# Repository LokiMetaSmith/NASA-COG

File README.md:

# NASA-MCOG

## Final Report

The final report delivered to NASA for this project can be [read here](https://drive.google.com/file/d/1jfJcSLfsybuC49I7llPhfTNI8ucRUW3h/view?usp=sharing).

## Introduction

This is a repo for a control system made for NASA to drive a Ceramic Oxygen Generation
technology they have developed. It was forked from ["The Ox"]() project of Public Invention run by Mr. Ben Coombs, which was in turn a fork of the VentOS project of Helpful Engineering led by Ben Coombs, Dr. Erich Schulz, and Robert L. Read.

However, the main reason we are starting with this fork is not that the Pressure Swing
Adsorption system of the Ox is a particularly relevant, but rather that the code
represents a nice platform of simple (microcontroller) control of related machines.

To wit, includes PlatformIO configuration, a state machine (finite automata),
a superloop architecture, and a hardware abstraction layer.

This particular project of NASA will improve life support technology in space,
but may eventually greatly improve global health.

An unlisted [YouTube video](https://youtu.be/1nq-Mw7jZ5A) has been uploaded that shows this work in-progress as of September 2022.

## How to run

### Linux
The fundamental way to run this is to perform:  
> cd firmware  
> pio run -e native && ./.pio/build/native/program  
We are currently creating the [RibbonFish](https://github.com/PubInv/NASA-COG/blob/develop/RibbonFish.md) proof-of-concept.
This can be run on a Due by executing:  
> make pio-run-due_ribbonfish  
As this develops, it will use a specific Due hardware configuration,  
please see the [documentation](https://github.com/PubInv/NASA-COG/blob/develop/RibbonFish.md) for details to build your own.  

### Windows
With Powershell
Navigate to the firmware folder. 
Type: pio run -e due_ribbonfish

With Visual Studio Code.  
Install the Plateform IO extension  
To open the project in Visual Studio Code.  
Open Project. Navigate to the firmware folder.   
Select the file platformio.ini  
Press the build check mark on the bottom of the window.

To disable the automatic load and serial monitor comment out the lines with "targets = upload, monitor" in the file "platformio.ini"

## Annoyances

AFAIK, PlatformIO forces a directory tree depth of 5 levels.

This is not enough to organize the Hardware Abstraction Level the way I would prefer, forcing us to make some messy directories that are less than clear.

For example, to implement a Temperature Sensor, we would ideally have an
abstract (or virtual) implementation, a folder for real hardware,
and a folder for mock sensors.  I have no choice now but to jam
the mock sensors into the same directory with the real hardware and
use a naming convention to differentiate them.

## The Command System

The NASA-COG system needs to allow the user to enter commands. The most obvious of these is "turn off".
Because the system should avoid thermal shocks, this is actually not simple.

We have previously used an [approach](https://github.com/PubInv/PIRCS-pubinv-respiration-control-standard) of using simple JSON objects to represent commands. We propose to use the same idea here, but obviously,
the command will be custom to the NASA-COG.

### Parameter Setting Commands
The general scheme is to use a JSON object like:

```JavaScript
{ "com": "T",
  "par": 7,
  "mod": "T",
  "val" : 732.3
  }
```

1. "com" is the command. For example, "T" can mean "set Temperature".
2. "par" is a parameter used to specify something about how to execute the command. For example, 7 could mean location 7, which might be between the 6th and 7th stack.
3. "mod" is a modifier of the command. For example, the "set Temperature" command could be used to
set the minimum, maximum, or the target temperature.
4. "val" is the value that is to be set.

For this problem space, we can specify some global parameters of the problem, some of which
involve safety. These can of course have default values "hard wired" into the code, but an
experimenter may wish to change these values (carefully).

1. The maximum rate of voltage change applied to a stack. Nominally we have defined this as 1 volt/second.
We have evidence that too rapid a voltage change (such as that caused by pulse-width modulation) can destroy
a stack.
2. The maximum rate of temperature change for a stack. Nominally we may say this as 2 degree K per minute,
which would allow the machine to reach operating temperature in 6 hours.
3. The maximum temperature difference across a stack in any dimension. We may not be able to control
this directly, but we can use it as a target.
4. The maximum voltage applied to a stack.
5. The maximum amperage applied to a stack.

### Event-like Commands

We will need other commands that represent discrete events in time. For example, each transition in the
state transition diagram below may be initiated by a command from the user (they may also occur
automatically due to an internal fault or even normal operation.)

We can implement particular commands with the same scheme.

For example, the simple object:

```JavaScript
{ "com": "C",
  "par": 0,
  "int": "s",
  "mod": "U",
  "val" : 0.0
  }
```

Could mean "Cool Down". The value "U" is used becasue the "mod" command is "unusued" in this case.

```JavaScript
{ "com": "W",
  "par": M,
  "int": "s",
  "mod": "U",
  "val" : 0.0
  }
```

In actual practice, these commands will be pasted into the serial port using either PlatformIO or the Arduino IDE.

Eventually, a user interface may be implemented that uses a knob or a nice webpage to enter commands.
However, by having each of these take only actions that can be implemented as such a command,
we bring discipline to the internal code.

## Actual Serial Commands

The serial port currently supports 6 one-character commands: w,c,e,a,i,o.
These mean:
1. warmup
2. cool down
3. emergency shutdown
4. acknowledge
5. idle
6. operate

Note: "acknowledge" means that the operator acknowledges that a critical
state has occurred and asserts it is okay to return to normal operation,
either because the problem as been removed or for some other reason.

Addtionally, the system supports "full commands", that look like this:

> { "com": "W", "par": "M", "int": "s", "mod": "U", "val" : 0.0 }

> { "com": "C", "par": "M", "int": "s", "mod": "U", "val" : 0.0 }

> { "com": "E", "par": "M", "int": "s", "mod": "U", "val" : 0.0 }

> { "com": "A", "par": "M", "int": "s", "mod": "U", "val" : 0.0 }

> { "com": "I", "par": "M", "int": "s", "mod": "U", "val" : 0.0 }

> { "com": "O", "par": "M", "int": "s", "mod": "U", "val" : 0.0 }

In fact, each "one character" command is a short hand for these commands.

The following format can be used to set parameters (P).
The three most important parameters are:
1. T : Temperature (in C) going into the stack
2. C : Current (in milliamps) going into the stack
3. F : Fan speed in RPM (we expect this to change to flow rate in SLM)
> { "com": "P", "par": "T", "int": "T", "mod": "U", "val" : 35 }

> { "com": "P", "par": "C", "int": "T", "mod": "U", "val" : 500 }

> { "com": "P", "par": "F", "int": "T", "mod": "U", "val" : 2000 }

These three commands set the:
1. Temperature into the stack to 35C
2. Set the Target current into the stack to 500 milliamps
3. Set the flow rate to 2000 ml/seconds

## License

In general we intend to follow the [Public Invention Licensed Guidelines](https://github.com/PubInv/PubInv-License-Guidelines) unless
NASA requests something different. If you are starting your own project, please
feel free to fork the license guidelines as a starting point if you like our
license policy.

This program includes free software: you can redistribute it and/or modify it under the terms of the GNU Affero General Public License as published by the Free Software Foundation, either version 3 of the License, or (at your option) any later version.

See the GNU Affero General Public License for more details. You should have received a copy of the GNU Affero General Public License along with this program. If not, see <https://www.gnu.org/licenses/>.

This program is distributed in the hope that it will be useful, but WITHOUT ANY WARRANTY; without even the implied warranty of MERCHANTABILITY or FITNESS FOR A PARTICULAR PURPOSE.

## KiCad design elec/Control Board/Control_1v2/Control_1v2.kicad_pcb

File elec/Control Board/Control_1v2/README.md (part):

# Contents of This Folder Copyed. MAKE NO MORE CHANGES HERE
See: https://github.com/PubInv/high-amp-controller-board
Copied on date: 20250526

<hr>
# Control V1.1 aka 1V1
Version 1.1 control board for NASA COG

On line schematic viewing from **Kicanvas** See: https://kicanvas.org  
The Control V1 is an Arduino DUE "Shield". The DUE will live below this printed wiring assembly. An Ethernet shield will live above as a "Socket". See KiCad Symbol & Footprint Library for Arduino Modules for "Shield" and "Socket"

## Schematics
### Browser page view of the schematic by KiCanvas.org 
Top page is "Control v1.kicad_sch". Note the page for MAX31856 is actualy for an MCP9600 but the page was not renamed (as of 20230830)
*  [Control1v1.kicad_sch](https://kicanvas.org/?github=https%3A%2F%2Fgithub.com%2FPubInv%2FNASA-COG%2Fblob%2Fdevelop%2Felec%2FControl%2520Board%2FControl_1v1%2FControl_1v1%2FControl_1v1.kicad_sch)
* [Adafruit-MAX31850-thermocouple-breakout-board.kicad_sch](https://kicanvas.org/?github=https%3A%2F%2Fgithub.com%2FPubInv%2FNASA-COG%2Fblob%2Fdevelop%2Felec%2FControl%2520Board%2FControl_1v1%2FControl_1v1%2FAdafruit-MAX31850-thermocouple-breakout-board.kicad_sch)
* [Adafruit-MAX31855-breakout-board.kicad_sch](https://kicanvas.org/?github=https%3A%2F%2Fgithub.com%2FPubInv%2FNASA-COG%2Fblob%2Fdevelop%2Felec%2FControl%2520Board%2FControl_1v1%2FControl_1v1%2FAdafruit-MAX31855-breakout-board.kicad_sch)
* [Adafruit-MAX31856-PCB-master.kicad_sch](https://kicanvas.org/?github=https%3A%2F%2Fgithub.com%2FPubInv%2FNASA-COG%2Fblob%2Fdevelop%2Felec%2FControl%2520Board%2FControl_1v1%2FControl_1v1%2FAdafruit-MAX31856-PCB-master.kicad_sch)
* [Fan controller.kicad_sch](https://kicanvas.org/?github=https%3A%2F%2Fgithub.com%2FPubInv%2FNASA-COG%2Fblob%2Fdevelop%2Felec%2FControl%2520Board%2FControl_1v1%2FControl_1v1%2FFan%2520controller.kicad_sch)
* [I2C_Level_Shifter.kicad_sch](https://kicanvas.org/?github=https%3A%2F%2Fgithub.com%2FPubInv%2FNASA-COG%2Fblob%2Fdevelop%2Felec%2FControl%2520Board%2FControl_1v1%2FControl_1v1%2FI2C_Level_Shifter.kicad_sch)
* [SPI_ControllerLevel_Shifter.kicad_sch](https://kicanvas.org/?github=https%3A%2F%2Fgithub.com%2FPubInv%2FNASA-COG%2Fblob%2Fdevelop%2Felec%2FControl%2520Board%2FControl_1v1%2FControl_1v1%2FSPI_ControllerLevel_Shifter.kicad_sch)
* [SSR Interface.kicad_sch](https://kicanvas.org/?https%3A%2F%2Fgithub.com%2FPubInv%2FNASA-COG%2Fblob%2Fdevelop%2Felec%2FControl+Board%2FControl+v1%2FSSR+Interface.kicad_sch=&github=https%3A%2F%2Fgithub.com%2FPubInv%2FNASA-COG%2Fblob%2Fdevelop%2Felec%2FControl%2520Board%2FControl%2520v1%2FSSR%2520Interface.kicad_sch)
* [display_interface.kicad_sch](https://kicanvas.org/?github=https%3A%2F%2Fgithub.com%2FPubInv%2FNASA-COG%2Fblob%2Fdevelop%2Felec%2FControl%2520Board%2FControl_1v1%2FControl_1v1%2Fdisplay_interface.kicad_sch)

## PCB / PWA
### Browser page view of the PCB by KiCanvas.org 
Printed Circuit Board, Printed Wiring Assembly
* [Control 1v1.kicad_pcb](https://kicanvas.org/?github=https%3A%2F%2Fgithub.com%2FPubInv%2FNASA-COG%2Fblob%2Fdevelop%2Felec%2FControl%2520Board%2FControl_1v1%2FControl_1v1%2FControl_1v1.kicad_pcb)

### PCB / PWA 3D Snapshot

### BOM and Parts List
File Notes:
See notes on the Gerbers, BOM and placement files at:
https://github.com/PubInv/NASA-COG/issues/342

## License, Public Invention for this PCB, PWA
* [Firmware: Affero GPL 3.0](https://www.gnu.org/licenses/agpl-3.0.en.html#license-text)
* [CERN Open Hardware Licence Version 2 - Strongly Reciprocal](https://ohwr.org/cern_ohl_s_v2.txt)

<hr> 

## KiCad Symbol & Footprint Library for Arduino Modules
<a href="./PICS/Rev2/PWA_FrontView.png">  
*Version 4.1.0*  

This is a library of KiCad schematic symbols and PCB footprints for most Arduino modules. You can use them to make your own PCB design which will effortlessly connect with your chosen Arduino module.

Currently included modules:
- Arduino **101** Shield
- Arduino **Due** Shield
- Arduino **Giga R1 WiFi** Shield
- Arduino **Leonardo** Shield
- Arduino **M0** Shield
- Arduino **M0 Pro** Shield
- Arduino **Mega 2560 R3** Shield
- Arduino **Micro** Socket
- Arduino **Mini** Socket
- Arduino **MKR 1000 WiFi** Socket
- Arduino **MKR WiFi 1010** Socket
- Arduino **MKR FOX 1200** Socket
- Arduino **MKR WAN 1300** Socket
- Arduino **MKR WAN 1310** Socket
- Arduino **MKR GSM 1400** Socket
- Arduino **MKR NB 1500** Socket
- Arduino **MKR Vidor 4000** Socket
- Arduino **MKR Zero** Socket
- Arduino **Nano** Socket
- Arduino **Nano 33 BLE** Socket / Tile
- Arduino **Nano 33 BLE Sense** Socket / Tile
- Arduino **Nano 33 BLE Sense R2** Socket / Tile
- Arduino **Nano 33 IoT** Socket / Tile
- Arduino **Nano Every** Socket / Tile
- Arduino **Nano RP2040 Connect** Socket / Tile
- Arduino **Nicla Sense ME** Socket / Tile
- Arduino **Nicla Vision** Socket / Tile
- Arduino **Nicla Voice** Socket / Tile
- Arduino **Pro Mini** Socket
- Arduino **Uno R1** Shield
- Arduino **Uno R2** Shield
- Arduino **Uno R3** Shield
- Arduino **Uno R3 SMD** Shield
- Arduino **Uno R4 Minima** Shield
- Arduino **Uno R4 WiFi** Shield
- Arduino **Uno WiFi R2** Shield
- Arduino **Zero** Shield
- Clone **Mega 2560 Pro** Socket
- Clone **Pro Mini** Socket

*"Shield" means the module is designed to plug in from beneath your PCB. "Socket" means the module is designed to plug in from above your PCB. "Tile" means the module is designed to be soldered directly on to your PCB using surface-mount pads.*

## KiCad Version Compatibility
This library requires at least KiCad 6 to function, and is tested on KiCad versions 6.0.8 and 7.0.2. Note that the installation procedure is different for KiCad 6 and 7; please see the [Library Installation](#library-installation) section below.

## Comments, Requests, Bugs & Contributions
All are welcome!
Please open an [Issue](https://github.com/Alarm-Siren/arduino-kicad-library/issues) or [Pull Request](https://github.com/Alarm-Siren/arduino-kicad-library/pulls), as appropriate.

## Library Installation
To install this library in your copy of KiCad, choose the correct section for your version of KiCad and follow the steps given. These instructions only cover automated installation using KiCad's built-in Package and Content Manager (PCM); manual installation is possible but not supported.

### KiCad 7

**Warning**: Do not change the nickname prefix from that given in step 4 below. If you do so KiCad will not assign the correct footprints to the symbols by default.

1. Open KiCad and open the Preferences window at "Preferences" -> "Preferences..."
2. Select the "Plugin and Content Manager" section in the left-hand pane.
3. Ensure that the "Automatically add installed libraries to the global lib table" option is ticked.
4. Ensure that the "Library nickname prefix" is set to "PCM_".
5. Ensuring that the "Check for package updates on startup" option is ticked is recommended. **(Optional)**
6. Click "OK" to close the Preferences window.
7. Click the "Plugin and Content Manager" button.
8. Select the "KiCad official repository" from the top drop-down box (if not already selected).
9. Go the Libraries tab and locate the "KiCad Library for Arduino Modules" in the list.
10. Click the "Install" button for that entry in the list.
11. Click "Apply Pending Changes".
12. Close the "Applying Package Changes" window once it has finished.
13. You should now find that this library is listed in the "Installed" tab.
14. Close the Plugin and Content Manager.
15. You may need to restart KiCad for the library installation to fully take effect. **(Optional)**
16. All done: you are now ready to use these schematic components and footprints in your projects!

### KiCad 6
**Recommendation:** If you can, you should upgrade to KiCad 7.

**Warning**: Do not change the Nicknames from those given in steps 12 and 18 below. If you do so KiCad will not assign the correct footprints to the symbols by default.

1. Open KiCad and click the "Plugin and Content Manager" button.
2. Select the "KiCad official repository" from the top drop-down box (if not already selected).
3. Go the Libraries tab and locate the "KiCad Library for Arduino Modules" in the list.
4. Click the "Install" button for that entry in the list.
5. Click "Apply Changes".
6. Close the "Applying Package Changes" window once it has finished.
7. You should now find that this library is listed in the "Installed" tab.
8. Close the Plugin and Content Manager.
9. Go to the "Preferences" -> "Manage Symbol Libraries..." menu option.
10. In the Symbol Libraries dialogue that appears, switch to the "Global Libraries" tab (if not already selected).
11. Click "Add empty row to table" button (the button with a big cross in it, beneath the table).
12. In the new line of the table, set the Nickname to "PCM_arduino-library", and ensure the Library Format is set to "KiCad".
13. In the same line of the table, set Library Path to "${KICAD6_3RD_PARTY}/symbols/com_github_alarm-siren_arduino-kicad-library/arduino-library.kicad_sym".
14. Click "OK" to close the Symbol Libraries dialogue.
15. Go to "Preferences" -> "Manage Footprint Libraries..." menu option.
16. In the Footprint Libraries dialogue that appears, switch to the "Global Libraries" tab (if not already selected).
17. Click "Add empty row to table" button (the button with a big cross in it, beneath the table).
18. In the new line of the table, set the Nickname to "PCM_arduino-library", and ensure the Library Format is set to "KiCad".
19. In the same line of the table, set Library Path to "${KICAD6_3RD_PARTY}/footprints/com_github_alarm-siren_arduino-kicad-library/arduino-library.pretty".
20. Click "OK" to close the Footprint Libraries dialogue.
21. All done: you are now ready to use these schematic components and footprints in your projects!

## Donations

I really hope you've found this library useful. If you'd like to buy me a beer in thanks for the work I put into it, you can make a donation using the button below:

## License & Legal
Copyright 2017-2023, [Nicholas Parks Young](https://github.com/Alarm-Siren).

Except as otherwise noted, all content of this library is licensed under the 
[Creative Commons Attribution-ShareAlike 4.0 International License](https://creativecommons.org/licenses/by-sa/4.0/), with the following additional exception:
> To the extent that the creation of electronic designs that use the Licensed Material can be considered to be Adapted Material, the Licensor waives Section 3 of the Public License with respect to these electronic designs and any generated files which incorporate data provided as part of the Licensed Material.

### "KiCad Library for Arduino" Banner & Icon

The two images "resources/banner.png" and "resources/icon.png" are licensed under the [Creative Commons Attribution-NonCommercial-ShareAlike 4.0 International License](https://creativecommons.org/licenses/by-nc-sa/4.0/). These images are derivatives of ["Arduino Open-Source Community: Main Logotype RGB Colors" originally created by Arduino](https://www.arduino.cc/en/trademark/community-logo). 

Original Images: Copyright 2013, [Arduino](https://www.arduino.cc/). Derived Images: Copyright 2023, [Nicholas Parks Young](https://github.com/Alarm-Siren).

### Arduino Trademark

The word "Arduino" is a registered trademark of [Arduino](https://www.arduino.cc/). This trademark is used in this library to refer to Arduino products and to identify Arduino-related non-commercial content, as permitted by Arduino's [trademark guidelines](https://www.arduino.cc/en/trademark). This project is not affiliated with nor endorsed by Arduino.

## FAQ

Answers to some common questions about this library.

### Is this library in active development?

Yes. For the foreseeable future, I will be providing support, bug-fixes and updating the library with any new Arduino modules as they are released.

### What does the license exception in the License & Legal section mean?

This library uses the same license as KiCad's own built-in parts library does, including the exception. The KiCad Libraries team have a [page which explains the meaning of the exception](https://www.kicad.org/libraries/license/). My version of the exception uses slightly better wording, but the effect is the same.

### Why do the footprints not have an `Edge.Cuts` outline?

If I put in an `Edge.Cuts` outline, then those users who want to have a PCB larger than the module footprint would have to modify the footprint to do so. In my experience, it is far more common for users to want a PCB larger than the module anyway, so I prefer to cater to those users. If you want your PCB to be the same size and shape as the Arduino module, you can trace the `F.Silkscreen` or `B.Silkscreen` layer (as appropriate) out in the `Edge.Cuts` layer yourself, or you can modify the footprint to change the outline from `F.Silkscreen` or `B.Silkscreen` layer to `Edge.Cuts`.

### Why do the Nicla Vision and Nicla Voice tile footprints have cut-outs?

The cut-outs are necessary to accommodate components on the back of those modules; without them the components would physically prevent you from getting the module's pads down to the footprint's SMD pads.

### Why does the whole footprint have an `F.Courtyard` or `B.Courtyard` outline? I can't place my components where I need to!

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
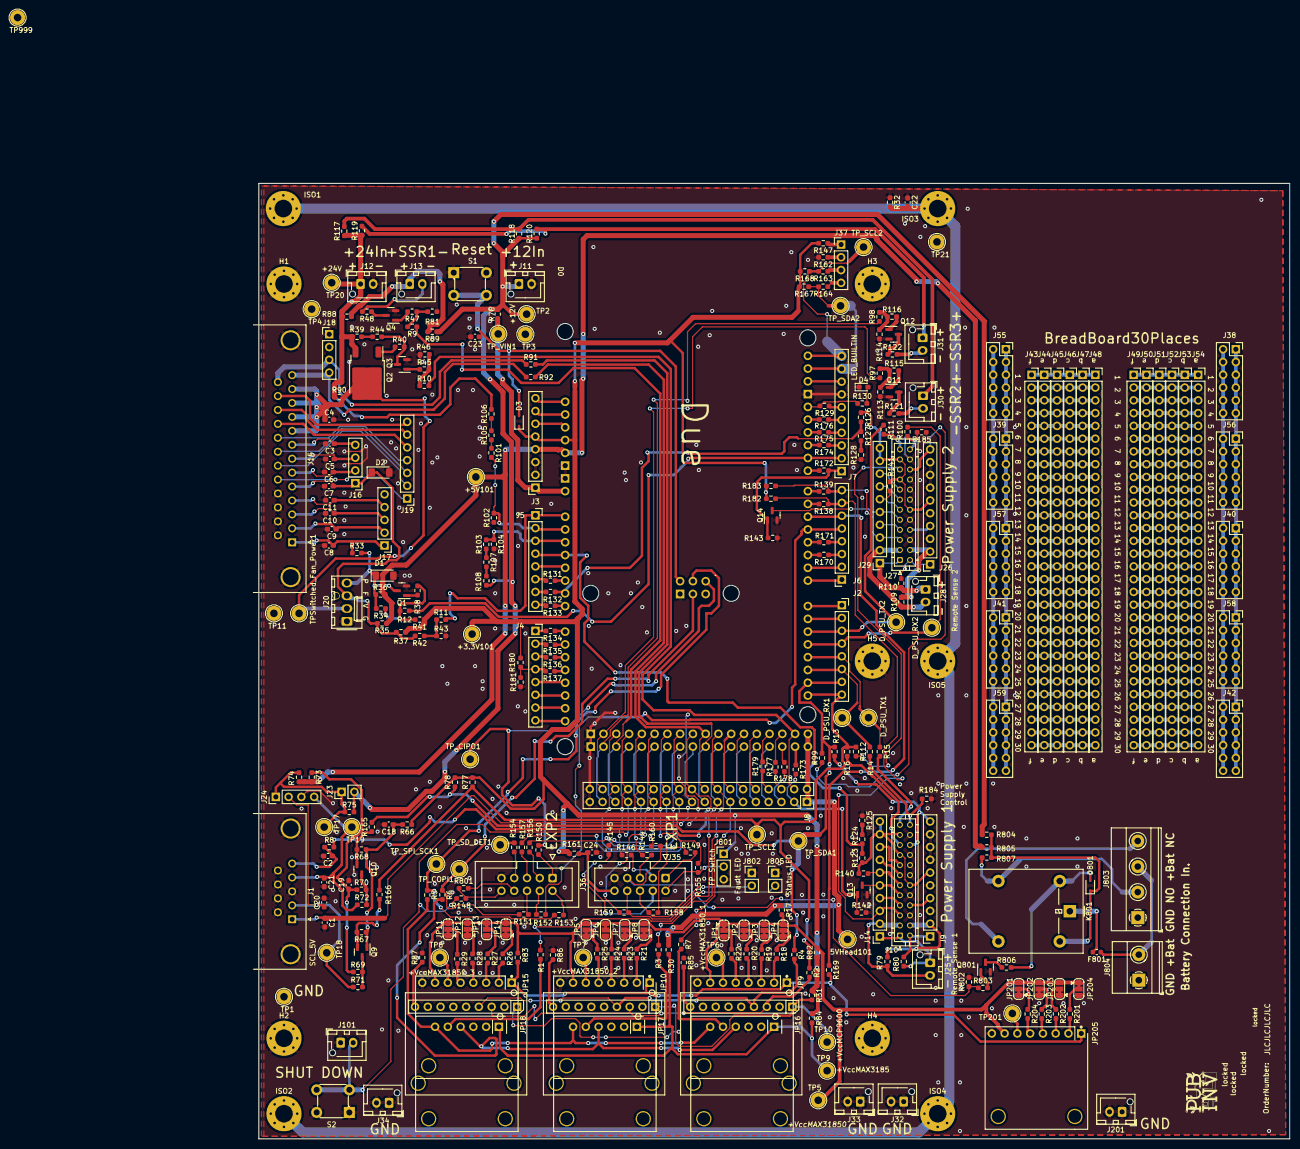
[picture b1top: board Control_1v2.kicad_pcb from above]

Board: 2 copper layers, 205.0 x 190.0 mm, 349 parts (0 on the bottom side), 342 nets.

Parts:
5VHead101: 5VHead; TestPoint_Loop_D2.54mm_Drill1.5mm_Beaded
+3.3V101: +3.3V; TestPoint_Loop_D2.54mm_Drill1.5mm_Beaded
+5V101: +5V; TestPoint_Loop_D2.54mm_Drill1.5mm_Beaded
A1: Arduino Due with Headers; Arduino_Due_Shield_Annotated
C1, C2, C3, C4, C5, C6, C7, C8, C9, C10, C11, C20, C21, C23: 39pF; C_0603_1608Metric_Pad1.08x0.95mm_HandSolder
C18, C19, C24: 1uF; C_0603_1608Metric_Pad1.08x0.95mm_HandSolder
C22: 10nF; C_0603_1608Metric_Pad1.08x0.95mm_HandSolder
D1, D2: 5.1V; D_MiniMELF
D3, D801: 1N5819WS; D_SOD-323
D4: RED 0603; LED_0603_1608Metric_Pad1.05x0.95mm_HandSolder
D_PSU_RX1: D_PSU_RX; TestPoint_Loop_D2.54mm_Drill1.5mm_Beaded
D_PSU_RX2: D_PSU_RX2; TestPoint_Loop_D2.54mm_Drill1.5mm_Beaded
D_PSU_TX1: D_PSU_TX; TestPoint_Loop_D2.54mm_Drill1.5mm_Beaded
D_PSU_TX2: D_PSU_TX2; TestPoint_Loop_D2.54mm_Drill1.5mm_Beaded
F801: Polyfuse_0603_1A; Fuse_0603_1608Metric
H1, H2, H3, H4, H5: MountingHole_Pad_3.5mm; MountingHole_3.5mm_Pad_Via
ISO1, ISO2, ISO3, ISO4, ISO5: MountingHole_Pad_3.5mm; MountingHole_3.5mm_Pad_Via
J1: DB9_Female_MountingHoles; DSUB-9_Female_Horizontal_P2.77x2.84mm_EdgePinOffset4.94mm_H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
J2, J3, J4, J5, J6: Conn_01x08; PinSocket_1x08_P2.54mm_Vertical
J7, J9, J14, J26, J29: Conn_01x10; PinSocket_1x10_P2.54mm_Vertical
J8: Conn_02x18_Odd_Even; PinSocket_2x18_P2.54mm_Vertical
J10, J27: Conn_02x12_Odd_Even; JST_PHD_B24B-PHDSS_2x12_P2.00mm_Vertical
J11, J12, J13, J25, J28, J30, J31, J32, J33, J34, J101, J201: Con_01x02_2.5mm; JST_XH_B2B-XH-AM_1x02_P2.50mm_Vertical
J15: DB25_Female_MountingHoles; DSUB-25_Female_Horizontal_P2.77x2.84mm_EdgePinOffset4.94mm_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
J16, J18, J24, J37: Conn_01x04; PinHeader_1x04_P2.54mm_Vertical
J17: Conn_01x05; PinHeader_1x05_P2.54mm_Vertical
J19: Conn_01x07; PinHeader_1x07_P2.54mm_Vertical
J20: Conn_01x04_KK-254_0470531000; Molex_KK-254_0470531000_1x04_P2.54mm_Vertical_ForFAN
J23, J802: Con_01x02_0.1; PinHeader_1x02_P2.54mm_Vertical
J35, J36: Conn_02x05_Odd_Even; IDC-Header_2x05_P2.54mm_Vertical
J38, J39, J40, J41, J42, J55, J56, J57, J58, J59: Conn_02x06_Odd_Even; PinSocket_2x06_P2.54mm_Vertical
J43, J44, J45, J46, J47, J48, J49, J50, J51, J52, J53, J54: Conn_01x30; PinSocket_1x30_P2.54mm_Vertical
J801: Conn_01x03_0.1; PinHeader_1x03_P2.54mm_Vertical
J803: Screw_Terminal_01x04_5.08mm; TerminalBlock_Phoenix_MKDS-1,5-4-5.08_1x04_P5.08mm_Horizont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
J804: Screw_Terminal_01x02_5.08mm; TerminalBlock_Phoenix_MKDS-1,5-2-5.08_1x02_P5.08mm_Horizont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
J805: Con_01x02_0.1"; PinHeader_1x02_P2.54mm_Vertical
JP1, JP2, JP3, JP4, JP5, JP6, JP7, JP8, JP11, JP12, JP13, JP14, JP201, JP202, JP203, JP204: SolderJumper_3_Bridged12; SolderJumper-3_P1.3mm_Bridged12_RoundedPad1.0x1.5mm
JP9, JP10, JP15, JP205: MAX31850K; Adafruit_MAX31850K_Module
JP16, JP17, JP18: MAX31855; Adafruit_MAX31855_Module
JP19, JP20, JP21: MCP9600; Adafruit_MCP9600_Module
K801: Relay SRU-12VDC; Relay_SPDT_Omron-G5LE-1
Q1, Q3, Q4, Q9, Q10, Q11, Q12, Q13, Q14, Q801: BSS138; SOT-23
Q2: NCE01P30K; TO-252-2
R1, R2, R3, R4, R5, R6, R7, R8, R9, R10, R11, R12, R13, R15, R16, R31, R33, R48, R66, R73, R76, R79, R80, R82, R84, R88, R91, R92, R97, R98, R99, R109, R110, R111, R112, R118, R119, R121, R122, R140, R141, R144, R145, R146, R147, R148, R149, R150, R151, R152, R153, R154, R155, R156, R157, R158, R159, R160, R161, R162, R163, R164, R165, R166, R169, R801, R804, R806, R807: 1R0; R_0603_1608Metric_Pad0.98x0.95mm_HandSolder
R14, R18, R19, R20, R21, R22, R23, R24, R25, R26, R27, R28, R29, R36, R37, R38, R42, R45, R47, R100, R115, R116, R130, R172, R173, R201, R202, R203, R204, R803: 1K; R_0603_1608Metric_Pad0.98x0.95mm_HandSolder
R17, R30, R34, R35, R43, R74, R75, R85, R86, R87, R89, R90, R120, R805: DNI; R_0603_1608Metric_Pad0.98x0.95mm_HandSolder
R32: 4M7; R_0603_1608Metric_Pad0.98x0.95mm_HandSolder
R39, R40, R41, R44, R46, R67, R68, R69, R70, R81, R101, R103, R104, R105, R107, R113, R114, R123, R124, R126, R127, R142, R143, R180, R182, R183, R802: 10K; R_0603_1608Metric_Pad0.98x0.95mm_HandSolder
R71, R72, R129, R131, R132, R133, R134, R135, R136, R137, R138, R139, R170, R171, R174, R175, R176, R177, R178, R179: 39R; R_0603_1608Metric_Pad0.98x0.95mm_HandSolder
R77, R78, R83, R102, R125, R128, R167, R168, R181: 4K7; R_0603_1608Metric_Pad0.98x0.95mm_HandSolder
R106, R108: 20K; R_0603_1608Metric_Pad0.98x0.95mm_HandSolder
R117: 1M; R_0603_1608Metric_Pad0.98x0.95mm_HandSolder
R184, R185: 2K; R_0603_1608Metric_Pad0.98x0.95mm_HandSolder
S1, S2: SWITCH_TACTILE_SPST-NO_0.05A_24V; Switch_Tactile_THT_6x6mm
TP1, TP3, TP4, TP11, TP21: GND; TestPoint_Loop_D2.54mm_Drill1.5mm_Beaded
TP2: +12V; TestPoint_Loop_D2.54mm_Drill1.5mm_Beaded
TP5: +VccMAX31850; TestPoint_Loop_D2.54mm_Drill1.5mm_Beaded
TP6: +VccMAX31850_1; TestPoint_Loop_D2.54mm_Drill1.5mm_Beaded
TP7: +VccMAX31850_2; TestPoint_Loop_D2.54mm_Drill1.5mm_Beaded
TP8, TP201: +VccMAX31850_3; TestPoint_Loop_D2.54mm_Drill1.5mm_Beaded
TP9: +VccMAX3185; TestPoint_Loop_D2.54mm_Drill1.5mm_Beaded
TP10: +VccMCP9600; TestPoint_Loop_D2.54mm_Drill1.5mm_Beaded
TP17: I2C_VCC; TestPoint_Loop_D2.54mm_Drill1.5mm_Beaded
TP18: SCL_5V; TestPoint_Loop_D2.54mm_Drill1.5mm_Beaded
TP19: SDA_5V; TestPoint_Loop_D2.54mm_Drill1.5mm_Beaded
TP20: +24V; TestPoint_Loop_D2.54mm_Drill1.5mm_Beaded
TP999: TestPoint; TestPoint_Loop_D2.54mm_Drill1.5mm_Beaded
TPSwitched_Fan_Power1: Switched_Fan_Power; TestPoint_Loop_D2.54mm_Drill1.5mm_Beaded
TP_CIPO1: CIPO; TestPoint_Loop_D2.54mm_Drill1.5mm_Beaded
TP_COPI1: COPI; TestPoint_Loop_D2.54mm_Drill1.5mm_Beaded
TP_SCL1: SCL; TestPoint_Loop_D2.54mm_Drill1.5mm_Beaded
TP_SCL2: SCL1; TestPoint_Loop_D2.54mm_Drill1.5mm_Beaded
TP_SDA1: SDA; TestPoint_Loop_D2.54mm_Drill1.5mm_Beaded
TP_SDA2: SDA1; TestPoint_Loop_D2.54mm_Drill1.5mm_Beaded
TP_SD_DET1: TP_SD_DET; TestPoint_Loop_D2.54mm_Drill1.5mm_Beaded
TP_SPI_SCK1: SPI_SCK; TestPoint_Loop_D2.54mm_Drill1.5mm_Beaded
TP_VIN1: VIN1; TestPoint_Loop_D2.54mm_Drill1.5mm_Beaded

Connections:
5VHead: 5VHead101.1, A1.5V3 (5V), A1.5V4 (5V), J8.1, J8.2, R17.1, R30.1
+3.3V: +3.3V101.1, A1.3V3 (3.3V), D3.1 (K), J3.5, J801.1, R31.1, R37.2, R41.1, R66.1, R77.2, R78.2, R82.1, R84.1, R147.2, R161.2, R167.2, R168.2, R180.1, R182.1, R183.1
+5V: +5V101.1, A1.5V1 (5V), J3.4, R35.1, R36.2, R73.2, R74.2, R805.1
+12V: J11.1, J23.2, R75.2, R76.1, R89.1, R108.2, R118.1, R120.1, R804.1, TP2.1
+24V: J12.1, Q2.3 (S), R39.1, R88.1, R90.1, R106.2, R117.1, R119.1, TP20.1
/ACI: J10.13, J14.7
/ACI2: J27.13, J29.7
/AUX: J9.6, J10.12, J10.17, J10.21, J14.9, J14.10, R123.1, R140.1
/AUX2: J26.6, J27.12, J27.17, J27.21, J29.9, J29.10, R126.1, R141.1
/Blower controller/FAN1_FG: R11.1, R42.1, R43.1
/Blower controller/FAN_POWER: R10.1, R45.2, R46.1
/Blower controller/LOOPBACK13: J15.13, J18.4, R92.1
/Blower controller/LOOPBACK25: J15.25, J18.3, R91.1
/Blower controller/PWMFan1: C8.1, J15.1, J17.1, R33.1
/Blower controller/PWMFan2: C9.1, J15.2, J17.2
/Blower controller/PWMFan3: C10.1, J15.3, J17.3
/Blower controller/PWMFan4: C11.1, J15.4, J17.4
/Blower controller/Switched_Fan_Power: C4.1, J15.9, J15.10, J15.11, J15.12, J20.2, Q2.2 (D), R90.2, TPSwitched_Fan_Power1.1
/Blower controller/TachFan1: C7.1, D2.1 (K), J15.5, J16.1, J20.3, R35.2, R37.1, R42.2
/Blower controller/TachFan2: C6.1, J15.6, J16.2
/Blower controller/TachFan3: C5.1, J15.7, J16.3
/Blower controller/TachFan4: C3.1, J15.8, J16.4
/Blower controller/nFAN1_PWM: R12.1, R34.1, R38.2, R41.2
/D_PSU_RX: A1.D19 (D19/RX1), D_PSU_RX1.1, J2.6, R14.1
/D_PSU_RX2: A1.D17 (D17/RX2), D_PSU_RX2.1, J2.4, R100.1
/D_PSU_TX: A1.D18 (D18/TX1), D_PSU_TX1.1, J2.5, R15.1
/D_PSU_TX2: A1.D16 (D16/TX2), D_PSU_TX2.1, J2.3, R111.1
/Display Interface/+3v3_local: C24.1, J35.10, R161.1
/Display Interface/BTN_EN1: J36.3, R156.2
/Display Interface/BTN_EN2: J36.5, R157.2
/Display Interface/BTN_ENC: J35.2, J801.2, R155.2
/Display Interface/Beeper: J35.1, R149.1
/Display Interface/LCD_MOSI/CS: J35.3, R146.1
/Display Interface/LCD_RS: J35.4, R145.1
/Display Interface/LCD_SCK: J35.5, R144.1
/Display Interface/LED_Blue: J35.8, J805.2, R159.2
/Display Interface/LED_Green: J35.7, R160.2, R802.1, R803.1
/Display Interface/LED_Red: J35.6, J802.2, R158.2
/Display Interface/RESET: J36.8, R801.2
/Display Interface/SD_CS: J36.4, R152.1
/Display Interface/SD_DET: J36.7, R154.1
/Display Interface/SD_MISO: J36.1, R150.1
/Display Interface/SD_MOSI: J36.6, R151.1
/Display Interface/SD_SCK: J36.2, R153.1
/Display Interface/STOP/KILL: J36.10, R148.1, R801.1
/EN2+: J27.11, J29.6, R141.2
/EN2-: J27.9, J29.5, Q14.3 (D)
/EN+: J10.11, J14.6, R140.2
/EN-: J10.9, J14.5, Q13.3 (D)
/I2C_LevelShift/+3V3Local: C18.1, Q9.1 (G), Q10.1 (G), R66.2, R67.1, R68.1
/I2C_LevelShift/+5VLocal: C19.1, R69.1, R70.1, R73.1
/I2C_LevelShift/I2C_VCC: J23.1, J24.1, R74.1, R75.1, TP17.1
/I2C_LevelShift/SCL_3.3V: Q9.2 (S), R67.2, R166.1
/I2C_LevelShift/SCL_5V: C20.1, J1.2, J24.2, R71.1, TP18.1
/I2C_LevelShift/SDA_3.3V: Q10.2 (S), R68.2, R165.1
/I2C_LevelShift/SDA_5V: C21.1, J1.4, J24.4, R72.1, TP19.1
/PAR: J10.7, J14.4
/PAR2: J27.7, J29.4
/PS2_SCL: J27.19, R112.2
/PS2_SDA: J26.10, J27.20, R99.1
/PS_SCL: J10.19, R16.2
/PS_SDA: J9.10, J10.20, R13.1
/RX: J10.23, R15.2
/RX2: J27.23, R111.2
/SD_CS: A1.D4 (D4_CS1), J6.5, R152.2
/SSR Interface/+VFan: J30.1, R117.2, R118.2
/SSR Interface/-VFan: J30.2, R121.2
/SSR Interface/Heater1: R9.2, R47.1, R81.1
/SSR Interface/Heater2: R97.2, R113.1, R115.1
/SSR Interface/Heater3: R98.2, R114.1, R116.1
/SSR Interface/SSR1+: J13.1, R88.2, R89.2
/SSR Interface/SSR1-: J13.2, R48.2
/SSR Interface/SSR3+: J31.1, R119.2, R120.2
/SSR Interface/SSR3-: J31.2, R122.2
/TX: J10.24, R14.2, R184.2
/TX2: J27.24, R100.2, R185.2
/Thermocouple Amplifier I2C breakout board - MCP9600/+VccMCP9600: JP19.1, JP20.1, JP21.1, R31.2, TP10.1
/Thermocouple Amplifier I2C breakout board - MCP9600/SCL: JP19.3, JP20.3, JP21.3, R2.2
/Thermocouple Amplifier I2C breakout board - MCP9600/SDA: JP19.4, JP20.4, JP21.4, R4.2
/Thermocouple Amplifier SPI Interface breakout board - MAX31855 /+VccMAX31855: JP16.1, JP17.1, JP18.1, R30.2, R84.2, TP9.1
/Thermocouple Amplifier SPI Interface breakout board - MAX31855 /DO: JP16.4, JP17.4, JP18.4, R6.2
/Thermocouple Amplifier SPI Interface breakout board - MAX31855 /SCK: JP16.6, JP17.6, JP18.6, R5.2
/Thermocouple Amplifier SPI Interface breakout board - MAX31855 /nCS_1: JP16.5, R7.2
/Thermocouple Amplifier SPI Interface breakout board - MAX31855 /nCS_2: JP17.5, R3.2
/Thermocouple Amplifier SPI Interface breakout board - MAX31855 /nCS_3: JP18.5, R1.2
/Thermocouple Amplifier with 1-Wire Breakout Board - MAX31850K/+VccMAX31850: JP1.1 (A), JP2.3 (B), JP3.3 (B), JP4.3 (B), JP5.3 (B), JP6.1 (A), JP7.3 (B), JP8.3 (B), JP9.7, JP10.7, JP11.3 (B), JP12.3 (B), JP13.1 (A), JP14.3 (B), JP15.7, JP201.3 (B), JP202.3 (B), JP203.3 (B), JP204.1 (A), JP205.7, R17.2, R82.2, R83.2, TP5.1
/Thermocouple Amplifier with 1-Wire Breakout Board - MAX31850K/DATA: JP9.1, JP10.1, JP15.1, JP205.1, R83.1, R169.1
/VCI: J10.15, J14.8
/VCI2: J27.15, J29.8
/VO2+: J26.1, J27.2, R110.2
/VO2-: J26.2, J27.4, R109.2
/VO+: J9.1, J10.2, R80.2
/VO-: J9.2, J10.4, R79.2
/VS2+: J27.1, J28.1, J29.1, R110.1
/VS2-: J27.3, J28.2, J29.2, R109.1
/VS+: J10.1, J14.1, J25.1, R80.1
/VS-: J10.3, J14.2, J25.2, R79.1
/VSET: J9.4, J10.8
/VSET2: J26.4, J27.8
/V_ASSY_VERSIONING: J4.4, R137.2, R180.2, R181.2
AREF: A1.AREF, J7.8
BLOWER_ENABLE: A1.D22, J8.4, R10.2
BLOWER_TACH: A1.A0, J5.1, R11.2
CANR: A1.CANR (CANRX), J4.7
CANT: A1.CANT (CANTX), J4.8
CIPO: A1.MISO (SPI_MISO), R150.2, TP_CIPO1.1
COPI: A1.MOSI (SPI_MOSI), R6.1, R151.2, TP_COPI1.1
D0: A1.D0 (D0/RX0), J6.1
D1: A1.D1 (D1/TX0), J6.2
D25: J8.5, R178.1
D27: A1.D27, J8.7
D29: A1.D29, J8.9
D31: A1.D31, J8.11
D32: A1.D32, J8.14
D37: A1.D37, J8.17, R91.2
D38: A1.D38, J8.20, R8.2
D39: A1.D39, C1.1, J1.1, J8.19
D40: A1.D40, J8.22, R156.1
D41: A1.D41, J8.21, R157.1
D42: A1.D42, J8.24, R155.1
D43: A1.D43, J8.23, R158.1
D44: A1.D44, J8.26, R159.1
D45: A1.D45, J8.25, R160.1
D46: A1.D46, J8.28, R144.2
D47: A1.D47, J8.27, R145.2
D48: A1.D48, J8.30, R146.2
D50: A1.D50, J8.32, R149.2
D51: A1.D51, J8.31, R9.1
D52: A1.D52 (D52_CS2), J8.34, R97.1
D53: A1.D53, J8.33, R98.1
DAC0: A1.DAC0, J4.5
DAC1: A1.DAC1, J4.6
GND: A1.GND1 (GND), A1.GND2 (GND), A1.GND3 (GND), A1.GND4 (SPI_GND), A1.GND5 (GND), A1.GND6 (GND), C1.2, C2.2, C3.2, C4.2, C5.2, C6.2, C7.2, C8.2, C9.2, C10.2, C11.2, C18.2, C19.2, C20.2, C21.2, C22.1, C23.2, C24.2, D1.2 (A), D2.2 (A), D4.1 (K), H1.1, H2.1, H3.1, H4.1, H5.1, J1.0 (PAD), J1.3, J1.6, J1.7, J1.8, J1.9, J3.2, J3.3, J7.7, J8.35, J8.36, J9.3, J9.5, J9.7, J9.8, J9.9, J10.6, J10.10, J10.14, J10.16, J10.18, J10.22, J11.2, J12.2, J15.0 (PAD), J15.14, J15.15, J15.16, J15.17, J18.1, J20.1, J24.3, J26.3, J26.5, J26.7, J26.8, J26.9, J27.6, J27.10, J27.14, J27.16, J27.18, J27.22, J32.1, J32.2, J33.1, J33.2, J34.1, J34.2, J35.9, J36.9, J101.1, J201.1, J201.2, J801.3, J802.1, J803.1, J804.1, J805.1, JP1.3 (B), JP2.1 (A), JP3.1 (A), JP4.1 (A), JP5.1 (A), JP6.3 (B), JP7.1 (A), JP8.1 (A), JP9.8, JP10.8, JP11.1 (A), JP12.1 (A), JP13.3 (B), JP14.1 (A), JP15.8, JP16.3, JP17.3, JP18.3, JP19.2, JP20.2, JP21.2, JP201.1 (A), JP202.1 (A), JP203.1 (A), JP204.3 (B), JP205.8, Q1.2 (S), Q3.2 (S), Q4.2 (S), Q11.2 (S), Q12.2 (S), Q13.2 (S), Q14.2 (S), Q801.2 (S), R32.1, R43.2, R46.2, R81.2, R85.1, R86.1, R87.1, R102.1, R104.2, R113.2, R114.2, R125.1, R128.1, R142.2, R143.2, R162.2, R181.1, R184.1, R185.1, R802.2, S1.1, S1.2, S2.1, S2.2, TP1.1, TP3.1, TP4.1, TP11.1, TP21.1
LED_BUILTIN: A1.D13, R129.2, R130.1
LOOPBACK13: A1.D36, J8.18, R92.2
unnamed: A1.D10 (D10_CS0), R174.2
unnamed: A1.D14 (D14/TX3), J2.1
unnamed: A1.D15 (D15/RX3), J2.2
unnamed: A1.IORF (IOREF), J3.7
unnamed: A1.A5, R131.1
unnamed: A1.A7, R133.1
unnamed: A1.A8, R134.1
unnamed: A1.A9, R135.1
unnamed: A1.A10, R136.1
unnamed: A1.A11, R137.1
unnamed: A1.D2, R170.2
unnamed: A1.D3, R171.2
unnamed: A1.D6, R138.2
unnamed: A1.D7, R139.2
unnamed: A1.D8, R172.1
unnamed: A1.D11, R175.2
unnamed: A1.D12, R176.2
unnamed: A1.D23, R173.1
unnamed: A1.D24, R177.2
unnamed: A1.D25, R178.2
unnamed: A1.D26, R179.2
unnamed: A1.RST1 (RESET), J3.6
unnamed: C2.1, J1.5, R8.1
unnamed: C22.2, ISO1.1, ISO2.1, ISO3.1, ISO4.1, ISO5.1, R32.2
unnamed: D1.1 (K), J20.4, Q1.3 (D), R33.2, R34.2, R36.1
unnamed: D4.2 (A), R130.2
unnamed: D801.2 (A), K801.2, R806.2
unnamed: D801.1 (K), K801.5, R804.2, R805.2, R807.1
unnamed: F801.2, K801.1
unnamed: A1.VIN, J3.1, R76.2, TP_VIN1.1
unnamed: A1.ND, J3.8
unnamed: J4.1, R134.2
unnamed: J4.2, R135.2
unnamed: J4.3, R136.2
unnamed: A1.A4, J5.5
unnamed: J5.6, R131.2
unnamed: J5.7, R132.2
unnamed: J5.8, R133.2
unnamed: J6.3, R170.1
unnamed: J6.4, R171.1
unnamed: J7.3, R174.1
unnamed: J7.4, R175.1
unnamed: J7.5, R176.1
unnamed: J7.6, R129.1
unnamed: J8.6, R177.1
unnamed: J8.8, R179.1
unnamed: A1.D28, J8.10
unnamed: A1.D30, J8.12
unnamed: J15.18, J19.1
unnamed: J15.19, J19.2
unnamed: J15.20, J19.3
unnamed: J15.21, J19.4
unnamed: J15.22, J19.5
unnamed: J15.23, J19.6
unnamed: J15.24, J19.7
unnamed: J37.1, R147.1
unnamed: J37.2, R162.1
unnamed: J37.3, R163.1
unnamed: J37.4, R164.1
unnamed: J38.1, J38.3, J38.5, J38.7, J38.9, J38.11, J40.1, J40.3, J40.5, J40.7, J40.9, J40.11, J42.1, J42.3, J42.5, J42.7, J42.9, J42.11, J56.1, J56.3, J56.5, J56.7, J56.9, J56.11, J58.1, J58.3, J58.5, J58.7, J58.9, J58.11
unnamed: J38.2, J38.4, J38.6, J38.8, J38.10, J38.12, J40.2, J40.4, J40.6, J40.8, J40.10, J40.12, J42.2, J42.4, J42.6, J42.8, J42.10, J42.12, J56.2, J56.4, J56.6, J56.8, J56.10, J56.12, J58.2, J58.4, J58.6, J58.8, J58.10, J58.12
unnamed: J39.1, J39.3, J39.5, J39.7, J39.9, J39.11, J41.1, J41.3, J41.5, J41.7, J41.9, J41.11, J55.1, J55.3, J55.5, J55.7, J55.9, J55.11, J57.1, J57.3, J57.5, J57.7, J57.9, J57.11, J59.1, J59.3, J59.5, J59.7, J59.9, J59.11
unnamed: J39.2, J39.4, J39.6, J39.8, J39.10, J39.12, J41.2, J41.4, J41.6, J41.8, J41.10, J41.12, J55.2, J55.4, J55.6, J55.8, J55.10, J55.12, J57.2, J57.4, J57.6, J57.8, J57.10, J57.12, J59.2, J59.4, J59.6, J59.8, J59.10, J59.12
unnamed: J43.1, J44.1, J45.1, J46.1, J47.1, J48.1
unnamed: J43.2, J44.2, J45.2, J46.2, J47.2, J48.2
unnamed: J43.3, J44.3, J45.3, J46.3, J47.3, J48.3
unnamed: J43.4, J44.4, J45.4, J46.4, J47.4, J48.4
unnamed: J43.5, J44.5, J45.5, J46.5, J47.5, J48.5
unnamed: J43.6, J44.6, J45.6, J46.6, J47.6, J48.6
unnamed: J43.7, J44.7, J45.7, J46.7, J47.7, J48.7
unnamed: J43.8, J44.8, J45.8, J46.8, J47.8, J48.8
unnamed: J43.9, J44.9, J45.9, J46.9, J47.9, J48.9
unnamed: J43.10, J44.10, J45.10, J46.10, J47.10, J48.10
unnamed: J43.11, J44.11, J45.11, J46.11, J47.11, J48.11
unnamed: J43.12, J44.12, J45.12, J46.12, J47.12, J48.12
unnamed: J43.13, J44.13, J45.13, J46.13, J47.13, J48.13
unnamed: J43.14, J44.14, J45.14, J46.14, J47.14, J48.14
unnamed: J43.15, J44.15, J45.15, J46.15, J47.15, J48.15
unnamed: J43.16, J44.16, J45.16, J46.16, J47.16, J48.16
unnamed: J43.17, J44.17, J45.17, J46.17, J47.17, J48.17
unnamed: J43.18, J44.18, J45.18, J46.18, J47.18, J48.18
unnamed: J43.19, J44.19, J45.19, J46.19, J47.19, J48.19
unnamed: J43.20, J44.20, J45.20, J46.20, J47.20, J48.20
unnamed: J43.21, J44.21, J45.21, J46.21, J47.21, J48.21
unnamed: J43.22, J44.22, J45.22, J46.22, J47.22, J48.22
unnamed: J43.23, J44.23, J45.23, J46.23, J47.23, J48.23
unnamed: J43.24, J44.24, J45.24, J46.24, J47.24, J48.24
unnamed: J43.25, J44.25, J45.25, J46.25, J47.25, J48.25
unnamed: J43.26, J44.26, J45.26, J46.26, J47.26, J48.26
unnamed: J43.27, J44.27, J45.27, J46.27, J47.27, J48.27
unnamed: J43.28, J44.28, J45.28, J46.28, J47.28, J48.28
unnamed: J43.29, J44.29, J45.29, J46.29, J47.29, J48.29
unnamed: J43.30, J44.30, J45.30, J46.30, J47.30, J48.30
unnamed: J49.1, J50.1, J51.1, J52.1, J53.1, J54.1
unnamed: J49.2, J50.2, J51.2, J52.2, J53.2, J54.2
unnamed: J49.3, J50.3, J51.3, J52.3, J53.3, J54.3
unnamed: J49.4, J50.4, J51.4, J52.4, J53.4, J54.4
unnamed: J49.5, J50.5, J51.5, J52.5, J53.5, J54.5
unnamed: J49.6, J50.6, J51.6, J52.6, J53.6, J54.6
unnamed: J49.7, J50.7, J51.7, J52.7, J53.7, J54.7
unnamed: J49.8, J50.8, J51.8, J52.8, J53.8, J54.8
unnamed: J49.9, J50.9, J51.9, J52.9, J53.9, J54.9
unnamed: J49.10, J50.10, J51.10, J52.10, J53.10, J54.10
unnamed: J49.11, J50.11, J51.11, J52.11, J53.11, J54.11
unnamed: J49.12, J50.12, J51.12, J52.12, J53.12, J54.12
unnamed: J49.13, J50.13, J51.13, J52.13, J53.13, J54.13
unnamed: J49.14, J50.14, J51.14, J52.14, J53.14, J54.14
unnamed: J49.15, J50.15, J51.15, J52.15, J53.15, J54.15
unnamed: J49.16, J50.16, J51.16, J52.16, J53.16, J54.16
unnamed: J49.17, J50.17, J51.17, J52.17, J53.17, J54.17
unnamed: J49.18, J50.18, J51.18, J52.18, J53.18, J54.18
unnamed: J49.19, J50.19, J51.19, J52.19, J53.19, J54.19
unnamed: J49.20, J50.20, J51.20, J52.20, J53.20, J54.20
unnamed: J49.21, J50.21, J51.21, J52.21, J53.21, J54.21
unnamed: J49.22, J50.22, J51.22, J52.22, J53.22, J54.22
unnamed: J49.23, J50.23, J51.23, J52.23, J53.23, J54.23
unnamed: J49.24, J50.24, J51.24, J52.24, J53.24, J54.24
unnamed: J49.25, J50.25, J51.25, J52.25, J53.25, J54.25
unnamed: J49.26, J50.26, J51.26, J52.26, J53.26, J54.26
unnamed: J49.27, J50.27, J51.27, J52.27, J53.27, J54.27
unnamed: J49.28, J50.28, J51.28, J52.28, J53.28, J54.28
unnamed: J49.29, J50.29, J51.29, J52.29, J53.29, J54.29
unnamed: J49.30, J50.30, J51.30, J52.30, J53.30, J54.30
unnamed: J803.2, K801.3, R807.2
unnamed: F801.1, J803.3, J804.2
unnamed: J803.4, K801.4
unnamed: JP1.2 (C), R22.1
unnamed: JP2.2 (C), R20.1
unnamed: JP3.2 (C), R19.1
unnamed: JP4.2 (C), R18.1
unnamed: JP5.2 (C), R25.1
unnamed: JP6.2 (C), R24.1
unnamed: JP7.2 (C), R23.1
unnamed: JP8.2 (C), R21.1
unnamed: JP9.2, R18.2
unnamed: JP9.3, R19.2
unnamed: JP9.4, R20.2
unnamed: JP9.5, R22.2
unnamed: JP9.6, TP6.1
unnamed: JP10.2, R21.2
unnamed: JP10.3, R23.2
unnamed: JP10.4, R24.2
unnamed: JP10.5, R25.2
unnamed: JP10.6, TP7.1
unnamed: JP11.2 (C), R29.1
unnamed: JP12.2 (C), R28.1
unnamed: JP13.2 (C), R27.1
unnamed: JP14.2 (C), R26.1
unnamed: JP15.2, R26.2
unnamed: JP15.3, R27.2
unnamed: JP15.4, R28.2
unnamed: JP15.5, R29.2
unnamed: JP15.6, TP8.1
unnamed: JP19.9, R85.2
unnamed: JP20.9, R86.2
unnamed: JP21.9, R87.2
unnamed: JP201.2 (C), R204.1
unnamed: JP202.2 (C), R203.1
unnamed: JP203.2 (C), R202.1
unnamed: JP204.2 (C), R201.1
unnamed: JP205.2, R201.2
unnamed: JP205.3, R202.2
unnamed: JP205.4, R203.2
unnamed: JP205.5, R204.2
unnamed: JP205.6, TP201.1
unnamed: Q1.1 (G), R38.1
unnamed: Q2.1 (G), R40.1
unnamed: Q3.3 (D), R40.2, R44.2
unnamed: Q3.1 (G), R45.1
unnamed: Q4.3 (D), R48.1
unnamed: Q4.1 (G), R47.2
unnamed: Q9.3 (D), R69.2, R71.2
unnamed: Q10.3 (D), R70.2, R72.2
unnamed: Q11.3 (D), R121.1
unnamed: Q11.1 (G), R115.2
unnamed: Q12.3 (D), R122.1
unnamed: Q12.1 (G), R116.2
unnamed: Q801.3 (D), R806.1
unnamed: Q801.1 (G), R803.2
unnamed: R39.2, R44.1
unnamed: R101.1, R105.1
unnamed: R103.1, R107.1
unnamed: R105.2, R106.1
unnamed: R107.2, R108.1
unnamed: R124.2, R125.2
unnamed: R127.2, R128.2
unnamed: R154.2, TP_SD_DET1.1
ONE_WIRE_TC: A1.D5, J6.6, R169.2
POK1: J6.7, J10.5, J14.3, R138.1, R182.2
POK2: J6.8, J27.5, J29.3, R139.1, R183.2
PS1_EN: J8.3, Q13.1 (G), R142.1, R173.2
PS2_EN: J7.1, Q14.1 (G), R143.1, R172.2
SCL: A1.D21 (D21/SCL), J2.8, R2.1, R16.1, R77.1, R112.1, R166.2, TP_SCL1.1
SCL1: A1.SCL1, J7.10, R163.2, R168.1, TP_SCL2.1
SDA: A1.D20 (D20/SDA), J2.7, R4.1, R13.2, R78.1, R99.2, R165.2, TP_SDA1.1
SDA1: A1.SDA1, J7.9, R164.2, R167.1, TP_SDA2.1
SENSE_12V: A1.A2, J5.3, R103.2, R104.1
SENSE_24V: A1.A1, J5.2, R101.2, R102.2
SENSE_AUX1: A1.A3, J5.4, R123.2, R124.1
SENSE_AUX2: A1.A6, R126.2, R127.1, R132.1
SHUTDOWN: A1.D49, J8.29, J101.2, R148.2, S2.3, S2.4
SPI_SCK: A1.SCK (SPI_SCK), R5.1, R153.2, TP_SPI_SCK1.1
SPI_nRST: A1.RST2 (SPI_RESET), C23.1, D3.2 (A), S1.3, S1.4
TC_nCS1: A1.D33, J8.13, R7.1
TC_nCS2: A1.D34, J8.16, R3.1
TC_nCS3: A1.D35, J8.15, R1.1
nFAN1_PWM: A1.D9, J7.2, R12.2

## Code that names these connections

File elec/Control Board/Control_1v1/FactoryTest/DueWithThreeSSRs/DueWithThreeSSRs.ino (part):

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#define SSR2 52
#define SSR3 53
#define SHUT_DOWN 49
#define LED_RED 43
#define LED_BLUE 44
#define LED_GREEN 45
#define BEEPER 50   //A buzzer.
#define nFAN1_PWM 9 // The pin D9 for driving the Blower.
#define BLOWER_ENABLE 22 // The pin D22 for Enable 24V to the Blower.

//Rotary Encoder on BigTreeTech MINI 12864
#define PIN_IN1 40
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#define ENC_SW 42   //A switch

// Programable Power Supply Enable
#define PS1_EN 23
#define PS2_EN 8


// Setup a RotaryEncoder with 2 steps per latch for the 2 signal input pins:
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  pinMode(SHUT_DOWN, INPUT_PULLUP);
  pinMode(ENC_SW, INPUT_PULLUP);
  pinMode(SSR3, OUTPUT);
  pinMode(BEEPER, OUTPUT);
  pinMode(BLOWER_ENABLE, OUTPUT);
  digitalWrite(BLOWER_ENABLE, HIGH); //Set high to enable blower power.
  analogWrite(nFAN1_PWM, 220);  // Set for low RPM
  //analogWrite(nFAN1_PWM, 128);  // Set for medium RPM
  pinMode(PS1_EN, OUTPUT);
  pinMode(PS2_EN, OUTPUT);
  digitalWrite(PS1_EN, HIGH); //Set high to enable PS1
  digitalWrite(PS2_EN, HIGH); //Set high to enable PS2
  // You can use Ethernet.init(pin) to configure the CS pin
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
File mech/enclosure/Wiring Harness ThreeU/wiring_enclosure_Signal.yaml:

#templates for generalized connectors
templates:
  - &template_stack
    type: Anderson Power SB50 SB
    subtype:  Dual
    pinlabels: [V+, V-, V+, V-]
  - &template_pressure
    type: '<a href="https://www.amazon.com/dp/B089YTG1SX/"> GX12-4 </a>'
    subtype: female
    pinlabels: [GND, VCC, SCL, SDA]
    notes: GX12 4 Pins Panel Metal Mount Circular Metal Aviation Connector Adapter Male Female Plug Socket with Waterproof Cap (5 Pcs)
    pn: Pressure Connector
    manufacturer: N/A
    mpn: GX12-4
    supplier: Amazon
    spn: '<a href="https://www.amazon.com/dp/B089YTG1SX/"> GX12-4 </a>'
    
  - &template_tc
    type: Molex KK 254
    subtype: female
    pinlabels: [GND, VCC, SCL, SDA]
    
  - &template_gnd
    type: Molex KK 254
    subtype: female
    pinlabels: [GND]
    
  - &template_heater
    type: Molex KK 254
    subtype: female
    pinlabels: [GND, L1, L2]
    
  - &template_led
    type: Molex KK 254
    subtype: female
    pinlabels: [GND, VCC]
    pn: CN2
    manufacturer: JST
    mpn: PHDR-24VS
    supplier: Digi-Key
    spn: 
    
  - &template_fan
    type: Molex KK 254
    subtype: female
    pinlabels: [GND, VCC, SCL, SDA]
    
  - &template_stack_wire
    gauge: 6.00 mm2
    length: 0.2
    colors: [RD,BK,RD,BK]
    category: bundle
    
  - &template_fan_wire
    gauge: 18 AWG
    length: 0.2
    colors: [RD,BK,RD,BK]
    category: bundle
    
  - &template_psu 
    type: PHDR-24VS
    subtype: female
    pincount: 24
    pinlabels: [VS+, VO+, VS-, VO-, POK, GND, PAR, VSET, EN-, GND, EN+, AUX, ACI, GND, VCI, GND, AUX, GND, SCL, SDA, AUX, GND, RX, TX]
    show_pincount: true
    pn: CN2
    manufacturer: JST
    mpn: PHDR-24VS
    supplier: Digi-Key
    spn: 455-1177-ND
    image:
      src: resources/PHDR-24VS.png
      caption: Power Supply Connector
      scale: width #(width height true/false) Expand image width to fill the available image cell space
      width:  200  # Expand image cell to this minimum width
      height: 100   # Expand image cell to this minimum height
      #scale: height # Expand image height to fill the available image cell space
      fixedsize: true #default value is false in this case
    
cables:   # dictionary of all used cables and wires
  W1:    # unique cable designator/name
    gauge: 6.0 mm2  # cable attributes (see below)
    # defaults to false; can auto-convert between mm2 and AWG and display the result when set to true
    show_equiv: true
     # <int/float> is assumed to be in meters unless <unit> is specified
                                # e.g. length: 2.5 -> assumed to be 2.5 m
                                # or   length: 2.5 ft -> "ft" is used as the unit
                                # Units are not converted during BOM generation;
                                # different units result in separate BOM entries.
    length: 0.5
    #color_code: IEC
    wirecount: 2
    category: bundle
    colors: [RD,BK]     # list of colors (see below)
    wirelabels: [V+,V-] # optional; one label for each wire
  W2:
    gauge: 0.25 mm2
    show_equiv: true
    length: 0.5
    color_code: IEC
    wirecount: 24
    category: bundle
  W3:
    gauge: 1 mm2
    show_equiv: true
    length: 0.5
    color_code: IEC
    wirecount: 3
    category: bundle
  W4:
    <<: *template_stack_wire
  W5:
    <<: *template_stack_wire
  W6:
    <<: *template_stack_wire
  
#PM - Panel Mount
#CN Connector, free hanging

connectors:  # dictionary of all used connectors
  CN1:  # unique connector designator/name
    style: simple
    autogenerate: true
    type: Crimp ferrule
    subtype: spade
    color: BU # blue
    image:
    notes: 
  
  CN2: 
    <<: *template_psu
  CN3:
    <<: *template_psu

  X1:
    type: D-Sub
    subtype: male
    pincount: 9
#    pinlabels: []

  X2:
    type: D-Sub
    subtype: male
    pincount: 25
    pinlabels: [NP,NP,NP,NP,PWM1,PWM2,PWM3,PWM4,+12v,+12v,+12v,+12v,NP,GND,GND,GND,GND,PWM5,PWM6,PWM7,PWM8,PWM9,PWM10,PWM11,NP]
    notes: Pin 5-8 have 470 Ohm Pull Up resistors
  X3:
    <<: *template_tc
  X4:
    <<: *template_tc
  X5:
    <<: *template_tc
  X6:
    <<: *template_tc
  Arduino_Mega:
    type: jumpers
    pinlabels: [A0, A1, A2, A3, A4, A5, A6, A7, A8, A9, A10, A11, A12, A13, A14, A15, D0, D1, D2, D3, D4, D5, D6, D7, D8, D9, D10, D11, D12, D13, D14, D15, D16, D17, D18, D19, D20, D21]
  X7:
    <<: *template_gnd
  X8:
    <<: *template_gnd
  X9:
    <<: *template_gnd
  X10:
    <<: *template_gnd
  X11:
    <<: *template_gnd
  X12:
    <<: *template_gnd
    
  SW1:
  SW2:
    type: SPDT switch
    notes: 110/220vAC 30 amp self lit switch
  
  FAN:
    <<: *template_fan
  LED1:
    <<: *template_led
  LED2:
    <<: *template_led

  USB1:
    type: USB B
    subtype: Receptacle 
    pincount: 4
    pinlabels: [+5V,D-,D+, GND]
  USB2:
    type: USB A
    subtype: Receptacle 
    pincount: 4
    pinlabels: [+5V,D-,D+, GND]
  USB3:
    type: USB A
    subtype: Plug
    pincount: 4
    pinlabels: [+5V,D-,D+, GND]
  USB4:
    type: USB Micro
    subtype: Receptacle 
    pincount: 5
    pinlabels: [+5V,D-,D+, GND]
  USB5:
    type: USB Micro
    subtype: Plug 
    pincount: 5
    pinlabels: [+5V,D-,D+, GND]
  ETH:
  CN4:
    type: C19
    subtype: male
    pincount: 3
    pinlabels: [L1,L2,GND]
    notes: C19
  CN5:
    type: C20
    subtype: female
    pincount: 3
    pinlabels: [L1,L2,GND]
    notes: C20
  CN6:
    type: C19 panel mount
    subtype: male
    pincount: 3
    pinlabels: [L1,L2,GND]
    notes: C19
  CN7: 
    type: C20 panel mount
    subtype: male
    pincount: 3
    pinlabels: [L1,L2,GND]
    notes: C20
  TC1:
    <<: *template_tc
  TC2:
    <<: *template_tc
  TC3:
    <<: *template_tc
  TC4:
    <<: *template_tc
    
connections:  # list of all connections to be made between cables and connectors
  -
    - ferrule_crimp
    - W1: [1-2]
    - ferrule_crimp
  -
    - CN2
    - W2: [1-24]
    - CN3
  -
    - CN4: [1-3]
    - [==, ==, ==]
    - CN5: [1-3]
  -
    - X1: [5,2,3]
    - W3: [1-3]
    - Arduino_Mega: [D0,D1,D21]
  -
    - X4: [1-4]
    - W4: [1-2]
    - W5: [1-2]
    - ferrule_crimp
  -
    - X1  # minimal connection set to include connector in the diagram
  -
    - USB1: [1-4]
    - [==, ==, ==, ==]
    - USB2: [1-4]
  -
    - USB3: [1-4]
    - [==, ==, ==, ==]
    - USB4: [1-4]
additional_bom_items:  # custom items to add to BOM
#  - zip ties           # BOM item (see below)
#  <key>   : <value>  # any number of key value pairs (see below)
  zip_ties : 30
  
  #...
metadata:  # dictionary of meta-information describing the harness
  #<key>   : <value>  # any number of key value pairs (see below)
  title: Iwiring diagram
  pn: WS-Front
  authors: Lawrence Kincheloe, 
  Created: 8/1/2024
  notes: https://www.amazon.com/dp/B09XK4JDBJ/
  more_notes: 1Ft Right Angle Micro USB Cable 3Pack 
  even more notes: Short USB A to Micro B Cord 90 Degree USB 2.0
  #...

#options:  # dictionary of common attributes for the whole harness
  #<str>   : <value>  # optional harness attributes (see below)
  #...

#tweak:  # optional tweaking of .gv output
 # ...

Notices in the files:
elec/Control Board/Control_1v1/FactoryTest/DueWithThreeSSRs/DueWithThreeSSRs.ino:
define LICENSE "GNU Affero General Public License, version 3 "
elec/Control Board/Control_1v2/Control_1v2.kicad_pcb:
GNU Affero General Public License v3.0
CERN Open Hardware License Version 2 - Strongly Reciprocal
elec/Control Board/Control_1v2/README.md:
CC BY-SA 4.0
CC BY-SA-NC 4.0
